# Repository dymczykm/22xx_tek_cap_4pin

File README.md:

# 4-pin cap adapter for Tektronix 22xx
An adapter for the 4-pin capacitor for Tektronix 22xx (2230, 2232 etc.) series. 4-pin caps are generally hard to come by these days and it's much easier to replace those with a modern Snap-In type.

## What does it fit?

The adapter should fit all 22xx with a switching power supply and a 270uF/450V cap (potentially others too). Definitely Tektronix 2232, 2230, 2245, 2245A, 2246, 2246A, 2247A, 2252.

## What is necessary?

Parts used:
- 1x LGW2W271MELC30 (Digikey: 493-8572-ND) Nichicon 270uF 450V 105*C cap, but others with similar dimensions will fit too
- 4x Harwin H2101-01 (Digikey: 952-1433-ND) pins

With these parts, the cap with an adapter nicely fits under the HV plastic shield and the pins are well aligned with the PCB.

## References

This project is loosely based on the existing project for 7xxx scopes:
https://github.com/peekpt/tekcaps

See also my personal page covering the topic:
https://dymczyk.com/tektronix-22xx-4-pin-cap-adapter

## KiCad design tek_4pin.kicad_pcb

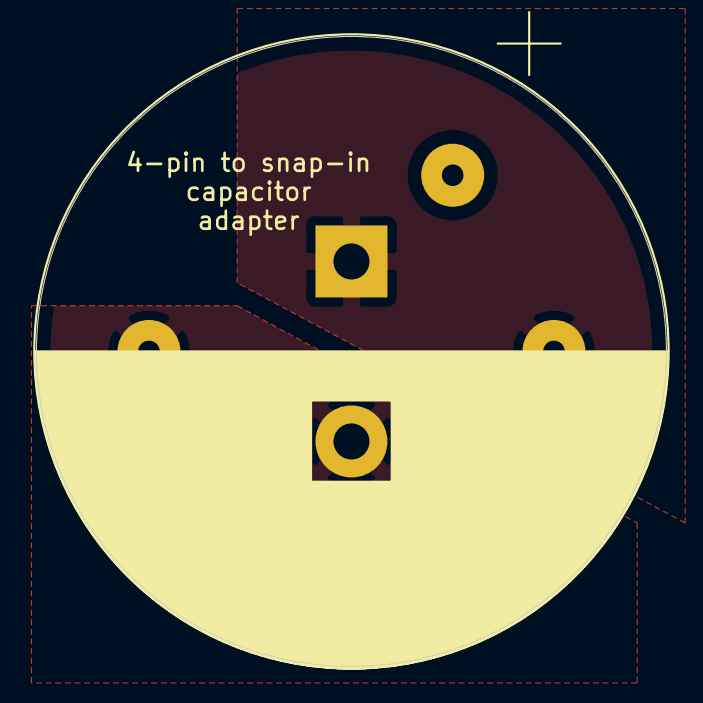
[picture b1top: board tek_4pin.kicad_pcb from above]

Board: 2 copper layers, 35.0 x 35.0 mm, 5 parts (0 on the bottom side), 2 nets, no tracks yet.

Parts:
C1: CP_Small; CP_Radial_D35.0mm_P10.00mm_SnapIn
H1, H2: MountingHole; SolderWirePad_1x01_Drill1.2mm
J1, J2: Conn_01x01_Female; SolderWirePad_1x01_Drill1.2mm

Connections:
unnamed: C1.1, J1.1
unnamed: C1.2, J2.1

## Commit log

2020-12-28 Commit kicad files and pictures.
2020-12-28 Scale down the images
